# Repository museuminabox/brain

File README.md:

# brain

You're probably looking for https://github.com/museuminabox/brain/blob/master/INSTALL.md.

When you get your Museum in a Box, the box knows which objects are in it and can tell you things about them. That's because of The Brain, a microcomputer like a Raspberry Pi. There are a few peripherals too, like an RFID reader, speakers, and a screen. The brain also keeps a note of any time an object comes across it. This is called the BOOP LOG.

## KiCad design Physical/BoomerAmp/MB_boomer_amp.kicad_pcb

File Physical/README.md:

# Physical Details of the Brain

This folder holds things relating to the physical instantiation of the Brain (rather than the software installed on it).

That includes things like the design files for laser-cut enclosures, and design files for [any custom PCB](BootProgressBoard/).

## Wiring

These wiring details use [this Raspberry Pi GPIO connector diagram](http://elinux.org/RPi_Low-level_peripherals#Model_A.2B.2C_B.2B_and_B2) for labels.

### RFID Reader

|Connector P1 (l-r)|Raspberry Pi|
|------------------|------------|
|VCC|+3V3|
|IN|Not connected|
|SDA|GPIO2/SDA1|
|SCL|GPIO3/SCL1|
|OUT|GPIO4|
|GND|GND|

### BootProgressBoard

|Connector P1 (l-r)|Raspberry Pi|
|------------------|------------|
|1|GPIO24|
|2|GPIO25|
|3|GPIO17|
|4|GPIO27|
|5|GPIO22|
|6|GPIO23|
|7|GPIO10|
|8|+3V3|
|9|GND|

### Raspberry Pi 2/3

Audio is provided by an amplifier board connected to the 3.5mm jack on the Pi.

See [here for a diagram showing the 3.5mm connections](http://www.raspberrypi-spy.co.uk/2014/07/raspberry-pi-model-b-3-5mm-audiovideo-jack/)

|Amp|3.5mm jack on the Pi|
|---|--------------------|
|Left|Tip|
|Right|Ring 1|
|Ground|Ring 2|
|Not connected|Sleeve|

### Raspberry Pi Zero

Audio is provided by a DAC board.  Either the [Pimoroni pHat DAC](https://shop.pimoroni.com/products/phat-dac) with stackable headers; or the [Adafruit I2S DAC/Amp board](https://learn.adafruit.com/adafruit-max98357-i2s-class-d-mono-amp/overview).

For the DAC/Amp the connections are as follows:

|DAC/Amp board|Raspberry Pi|
|-------------|------------|
|LRC|GPIO19/MISO|
|BCLK|GPIO18|
|DIN|SCLK/GPIO21|
|GAIN|Not connected|
|SD|Not connected|
|GND|GND|
|Vin|+5V|

Because the DACs don't have volume controls, we add two buttons for volume up and down.  They're connected as follows (l-r in [this photo](https://www.flickr.com/photos/amcewen/31221595945/)):

|Volume board|Raspberry Pi|
|------------|------------|
|Volume up|GPIO6|
|Volume down|GPIO13|
|Ground|GND|
|Pin with neither button but both resistors|Not connected|

## Assembly

This isn't necessarily the *only* way to assemble the Brain, but the general order that we've taken.

### Assemble "base of the skull"

1. Assemble an [audio circuit](#Wiring_the_audio_circuit)
1. Assemble an amp-to-speaker wiring loom
1. Carefully bend the terminals on the speaker so that they form a right-angle
1. Test assemble the speaker frame and then glue it together with the speaker inside
1. Plug in the 3.5mm audio jack to connect the audio circuit to the Raspberry Pi
1. Fit the rivets into the base first
1. Push Raspberry Pi down onto the rivets in the base

### Assemble "top of the skull"

1. Lay out all the components to check that you've got everything.
1. Insert the 4 t-nuts into the base of the top
1. Solder the right-angle header onto the RFID reader
1. Test assemble the RFID reader frame, and then glue together
1. Check the fit for the pieces making up the main box
1. Glue together the pieces for the main box, apart from the top
1. Once the main box is dry, glue in the top
1. Sand down the box (if it's not acrylic)
1. Apply one or two coats of Danish oil to the box (similarly if it's not acrylic)

### Wiring the Boot Progress PCB

1. Solder up the Boot Progress Board PCB

### Wiring the audio circuit

1. For the analogue amplifier Brains, solder header pins into the amplifier
1. We use pre-assembled [cables connected to a TRRS 4-pole 3.5mm jack plug](http://uk.farnell.com/cliff-electronic-components/fc68122c/cable-assembly-jack-plug-4-way/dp/2470995?CMP=i-bf9f-00001000) to connect to the Pi, so check that which wire colour goes to which pole on the plug.  If you're soldering your own wires to a 3.5mm plug, then obviously you'll know which is which.  In our case the colour-coding is:
  * Tip: red
  * Ring 1: white
  * Ring 2: black
  * Sleeve: shielding
  Or for the double-ended cables we're using in v1, the colour-coding is:
  * Tip: red
  * Ring 1: white
  * Ring 2: green
  * Sleeve: blue or black
1. Assuming you're using the same [3.5mm switched audio jack](http://www.digikey.co.uk/product-detail/en/cui-inc/SJ1-3535/CP1-3535-ND/738693) as we do, then connect the following connections to wire the 4-pole TRRS plug to the aux audio jack:
  * Tip (red) to connection 2
  * Ring 1 (white) to connection 3
  * Ring 2 (black/green) to connection 1
  * Sleeve is left unconnected
1. If you're using the same amplifier board as us, you should desolder the audio jack from it.  When you have, the connections&mdash;when viewed from underneath, from left to right&mdash;are tip \ sleeve / ring (on a TRS stereo jack)
1. Wire the output connections of the aux jack to the amplifier, with ~20cm of cable.  We'll leave the ground connection unconnected as it will prevent a ground loop with the ground connection for power.
  * Connection 4 (red) to the left audio input
  * Connection 5 (white) to the right audio input

### Prep the amp-to-speaker wiring loom

1. Cut a 15cm length of 2-core cable
1. Bare ~5mm of wire at one end and tin the end
1. Bare ~10mm of wire at the other end
1. Insert the longer bared ends through the loops on the terminals on the speaker (if you've got coloured wire, red to positive and black to negative) then fold it back on itself to make a decent physical connection.  Then solder the wires to the speaker terminal

### Assemble main wiring loom

1. Get the RFID to Pi connector cable
1. Wire a two-pin shroud to the 5V and ground connection on the RFID reader shroud to break out power from the Raspberry Pi to the amplifier
1. Assemble the Boot Progress PCB wiring loom with 9-pin shroud and [connections as detailed above](#BootProgressBoard)

### Assembly
1. Fasten the USB extension cable into the main box
1. Connect up all the electronics and make sure it's all working before it gets installed fully
1. Fit the amp and 3.5mm jack socket into the main box
1. Hot-glue the boot progress board into the main box

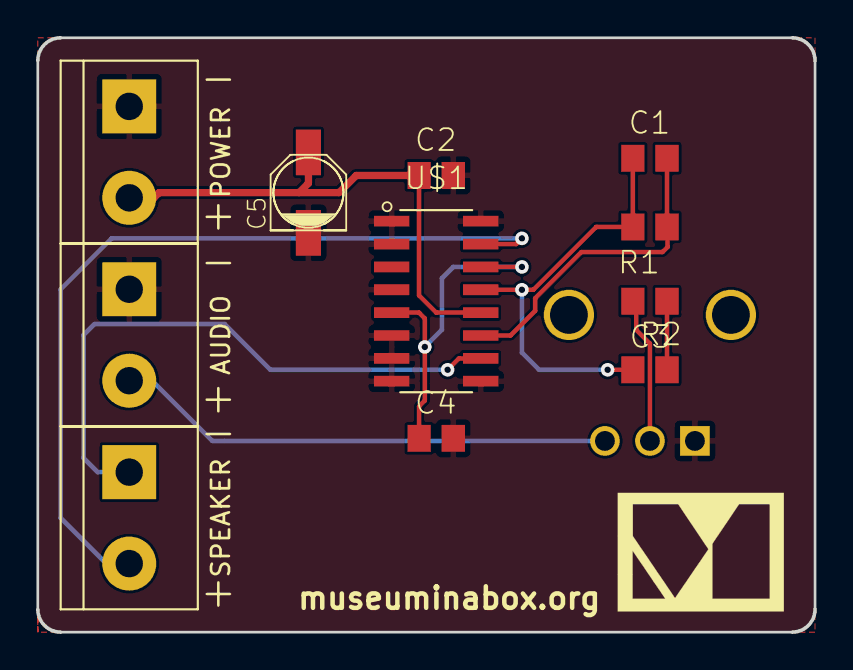
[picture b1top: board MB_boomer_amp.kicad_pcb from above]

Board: 2 copper layers, 43.2 x 33.0 mm, 12 parts (0 on the bottom side), 10 nets.

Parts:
AUDIO: GREEN-2P-3.5; TerminalBlock_bornier-2_P5.08mm
C1: 5p; C0805
C2, C4: 100n; C0805
C3: 4.7u; C0805
C5: 10u; PANASONIC_B
POWER: GREEN-2P-3.5; TerminalBlock_bornier-2_P5.08mm
R1: 100k; R0805
R2: 10k; R0805
SPEAKER: GREEN-2P-3.5; TerminalBlock_bornier-2_P5.08mm
U$1: LM4860; SOIC127P600X175-16
VR1: 9MM_SNAP-IN_POT_; 9MM_SNAP-IN_POT

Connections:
/ASIG: AUDIO.2, VR1.3
/VCC: C2.1, C5.+, POWER.2, U$1.12
GND: AUDIO.1, C2.2, C4.2, C5.-, POWER.1, U$1.1, U$1.2, U$1.4, U$1.6, U$1.7, U$1.8, U$1.9, U$1.16, VR1.1
unnamed: C1.1, R1.2, R2.1, U$1.13
unnamed: C1.2, R1.1, U$1.11
unnamed: C3.1, R2.2
unnamed: C3.2, VR1.2
unnamed: C4.1, U$1.5, U$1.14
unnamed: SPEAKER.1, U$1.10
unnamed: SPEAKER.2, U$1.15

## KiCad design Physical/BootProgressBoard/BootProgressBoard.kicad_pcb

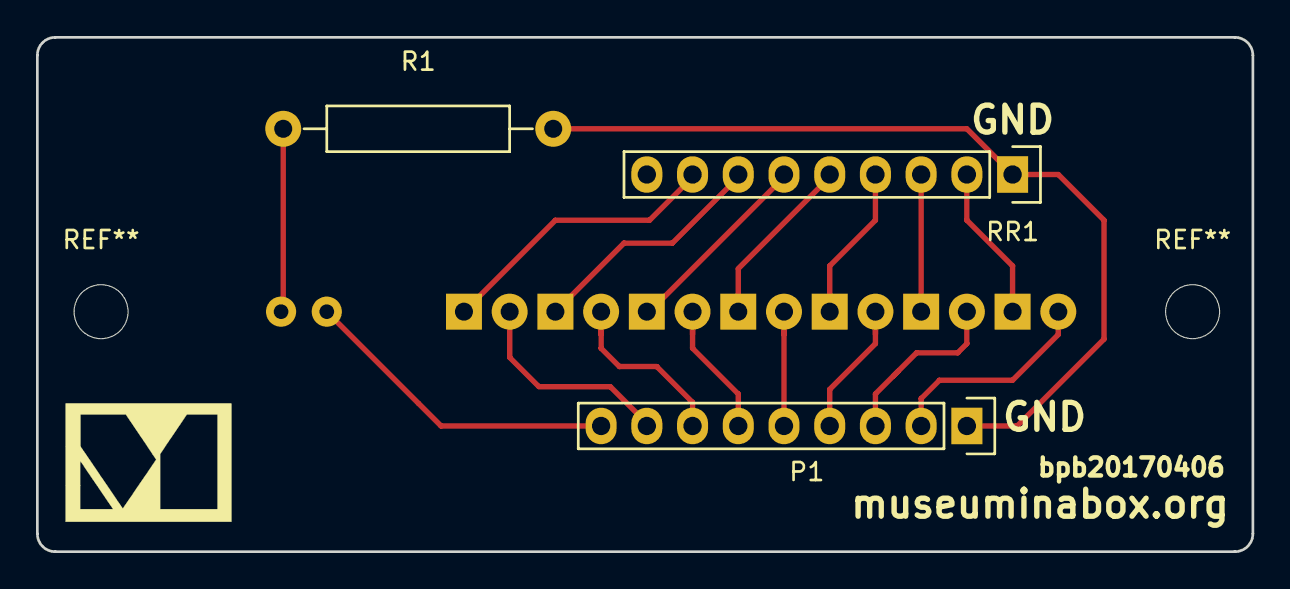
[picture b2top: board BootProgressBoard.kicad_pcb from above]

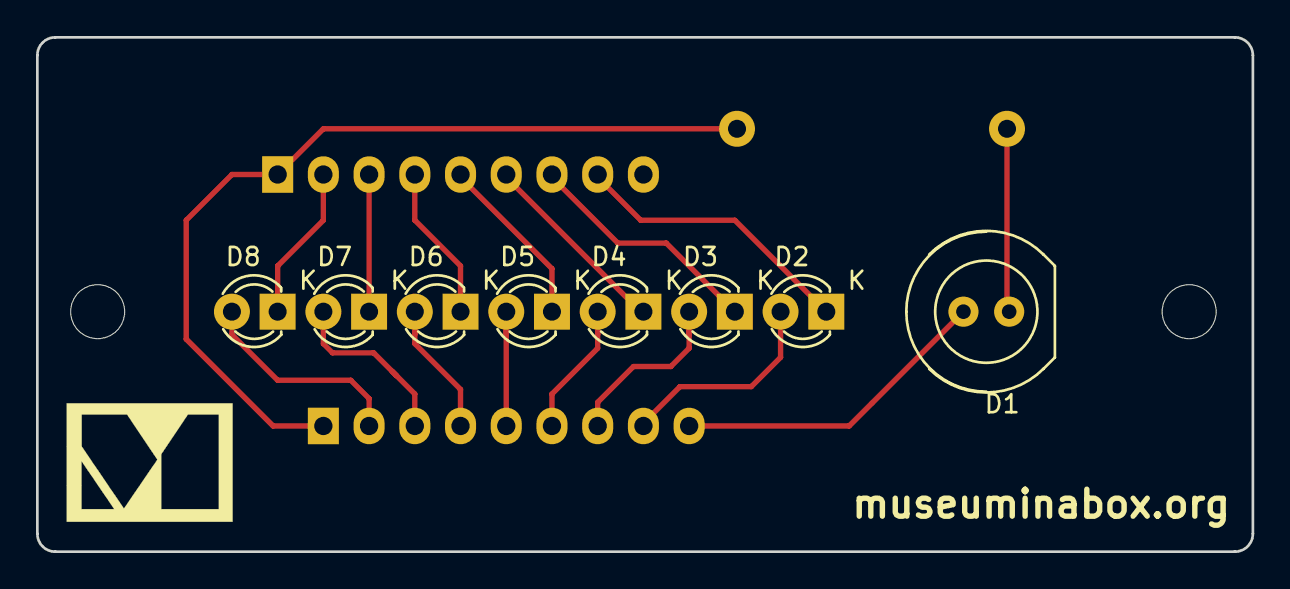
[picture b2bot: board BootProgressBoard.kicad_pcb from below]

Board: 2 copper layers, 67.5 x 28.6 mm, 11 parts (8 on the bottom side), 17 nets.

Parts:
D1: LED; LED-8MM
D2, D3, D4, D5, D6, D7, D8: LED; LED-3MM
P1: CONN_01X09; Socket_Strip_Straight_1x09
R1: R; Resistor_Horizontal_RM15mm
RR1: RR8; Socket_Strip_Straight_1x09

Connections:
unnamed: D1.1, R1.1
unnamed: D1.2, P1.9
unnamed: D2.1, RR1.8
unnamed: D2.2, P1.8
unnamed: D3.1, RR1.7
unnamed: D3.2, P1.7
unnamed: D4.1, RR1.6
unnamed: D4.2, P1.6
unnamed: D5.1, RR1.5
unnamed: D5.2, P1.5
unnamed: D6.1, RR1.4
unnamed: D6.2, P1.4
unnamed: D7.1, RR1.3
unnamed: D7.2, P1.3
unnamed: D8.1, RR1.2
unnamed: D8.2, P1.2
unnamed: P1.1, R1.2, RR1.1

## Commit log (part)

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2015-12-01 Initial version.
2015-12-01 Add Node RED flow for the video brain.
2015-12-01 Add Node RED flow for the audio brain.
2015-12-01 Extend form entry fields.
2015-12-01 Add instructions for writing tags
2015-12-07 Add laser-cutting file for self-contained MiaB.
2015-12-07 Log Boops to local CSV and web (for video boxes)
2015-12-07 Update audio version to submit Boops to the cloud.
2015-12-10 Add script to ease writing RFID tags.
    Needs libfreefare, and a PN532 USB NFC reader (or presumably something else that libfreefare/libnfc can drive)
2016-04-02 Make brain setup easier. Most of issue #17.
    Merge audio and video flows together - chooses behaviour at run time based on context.global.box_settings.brain_type
    Load settings (from /home/pi/miab/box-config.json) on startup and store them in context.global.box_settings
    Add a web UI '/setup' which downloads a list of boxes from www.museuminabox.org and gives you a simple drop-down menu to choose which box this brain is inside
    Add a web UI '/prints' (which you get redirected to from a successful submission on '/setup') which lists prints for this box and provides a 'Write tag' button next to each
    Add code to write print's NFC tag content to a tag when the 'Write tag' button is clicked
2016-04-11 Added more detailed instructions for WiFi 📡
2016-04-11 Add downloading of Brain content from website, playing ready.wav when the brain is ready to work
2016-05-12 Update for battery & volume control version of the brain.
2016-05-13 Add the display card template and other handy-but-non-essential files.
2016-05-20 Faster tag recognition by using the GPIO "tag present" signal.
2016-05-25 Added some labels and explanation to the case design
2016-05-25 Move object-detected-boop to only happen with video Brains
2016-05-25 Add files to indicate boot progress
2016-06-08 Add frog case design.
2016-06-15 Start ansible configuration for bootstrapping a Brain.
2016-07-12 Finish provisioning brains via ansible.
    Two roles created:
    * A base Node RED install
    * A Node RED install with an RFID reader
    Then sets up the MiaB brain on top of that.
    Boot progress script moved to systemd (in line with newer Raspbian)
    NDEF reading C program from simple_sl030_rfid_reader compiled and included in the miab/ folder, along with a service to copy the correct one to a common filename on boot (so will work regardless of t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
2016-08-16 Update RFID reading binary to work better on a Pi3
2016-08-23 Fix a couple of bugs in the ansible script.
    Bits missed during development as I'd obviously installed things and/or run Node RED before working out which files were needed. Running through the process from a bare SD card showed up a few bits t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
2016-09-06 Switch back to wpa_supplicant.conf (from wicd-curses) for WiFi management
2016-09-08 Finished provisioning work.
    * /setup now correctly downloads all the content when run, rather than needing to wait for next boot (was passing through parts of old web requests to the "download list of box contents" request, whi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
    * Hostname is set to brain
2016-09-22 Add soundcard configuration to use a Phat DAC on the Pi Zero
2016-09-22 Switch to sox for audio playback (copes with different sample rates)
2016-09-22 Set volume to max during provisioning. Fixes #28
2016-09-22 Pre-set the content folders so they don't end up owned by root. Fixes #27
2016-09-28 Stop git caring about brain images
2016-09-28 Add micro:bit code for Brain to talk to microbit-miab
2016-09-28 Update case to micro-USB power, using Boot Progress Board PCB
2016-09-28 Add spacer to make the LEDs line up better above the PCB
2016-10-04 Set up USB sound card as the one to use for recording
2016-10-17 Just replacing after a George github tutorial
2016-10-19 MVP of recording user content.
    The replay/delete/save buttons are accessed at http://brain.local:1880/ rather than as physical buttons at present.
2016-11-07 Change user the boot progress script runs as, so the LEDs light up again.
2016-12-06 Add wiring instructions
2017-03-03 Change booting sound files to Gill
2017-03-03 First pass at Pi3 timings for boot progress
2017-03-17 Add instructions for using the pre-rolled image files
2017-03-17 Tweak the volume level for the brains
2017-03-17 Update progress/ready audio cues (to Gill)
2017-03-27 Tweaks for RPi3 timings for the LEDs. Fixes #25
2017-03-27 Set umask so downloaded content can be modified by the pi user. Fixes #32
2017-04-11 Drop www. from URL, move logo & URL
2017-07-17 Gill's intro script
2017-09-13 Latest version
2017-09-13 Add assembly instructions
2017-09-13 Work-in-progress WiFi config. Start of Resin-wifi-connect addition.
    Manual steps required afterwards:
    * Run through the steps in the Dockerfile
    * Mod /usr/src/app/src/hotspot.js to stop the dnsmasq service before the hotspot is created
2017-09-13 Add w-i-p service file to start the WiFi config at boot
2017-09-13 Move Gill intro audio to where the Brains can play it.
2017-09-25 Make pre-rolled image install docs section clearer
2018-01-12 rough startup scripts
2018-02-14 Set WiFi settings for known networks
2018-02-14 Use a special RFID tag to launch wifi configuring.
    Also fixed bug so it plays the right message when the WiFi config script starts.
    And add ability to write the config tags to http://brain.local:1880/prints
2018-02-15 Remove unused wifi configure service script
2018-02-24 Remove support for video playback. Fixes #44
2018-02-24 Revert to original version of raspi_version.py. Fixes #42
2018-02-26 Change boop example to reflect reality
2018-02-28 Add updates about UUIDs.
2018-03-02 Move to new box creation workflow. Part of #52.
    Not fully tested yet because the corresponding Heart API hasn't been built.
2018-03-07 Record boop ends as well as boop starts. UNTESTED. Part of #40
    Need the corresponding part in the Heart app to be implemented before we can test this.
2018-03-07 Change computer name from 'brain' to 'box'. Fixes #53
2018-03-13 Rework wiring loom for simpler assembly. Fixes #57
2018-03-14 Move to new heart.museuminabox.org/api endpoints and avoid startup race condition.
    * Fixes #26 - point at heart.museuminabox.org
    * Fixes #60 - move API calls to /api/...
    * Fixes #61 - race condition at startup
2018-03-14 Fix bug where the headers weren't set for the box creation call. Now tested and working, last part of #52
2018-03-14 Update details for Boop start and end endpoints
2018-03-14 Formatting fix
2018-03-15 Add hardware_id details.
2018-03-15 Add hardware_id and exterior etc.
2018-03-15 Fix List of Prints response
2018-03-15 Submit hardware_id and exterior when creating a box, and send boop_id when boops end.
    Fixes #63 - store hardware_id and exterior
    Fixes #42 - boop ends and boop starts recorded
2018-03-15 Add software versioning. UNTESTED Needs corresponding Heart changes.
    Most of #56
2018-03-15 Fix Box Sync endpoint (only UUIDs)
2018-03-21 Updates to build instructions following the latest round of manufacturing
2018-04-11 Add `/upgrade` option. Fixes #64. Also shows existing ID if set. Fixes #71
2018-04-13 WiFi config now gives up after 2 mins, and tells you if it worked or not. Fixes #67
2018-04-13 Change WiFi branding to MiaB. Fixes #72
2018-04-13 copy tweaks
2018-04-14 Improve display of `/prints` screen. Part of #73
2018-04-14 Speed up boot progress bar now OS is faster to boot. Part of #65
2018-04-14 Add simple upgrade process. First pass at #55.
    Also fixed print image display on `/prints`, part of #73
2018-04-14 Change default password. First fix for #54
2018-04-14 Update version number for the latest features.
2018-05-21 Add work-around Wifi config for 802.1x networks. Part of #78
2018-05-21 Bump version number for work-around wifi config changes.
2018-05-29 Add instructions for configuring wifi and checking for updates.
2018-05-29 Fix links to embedded images
2018-10-09 we need to document a whole bunch more
    about what "componentry" entails and how to get it attractively arranged :)
2018-10-22 Initial version of the amp PCB. Part of #86
2018-11-04 Add logo to the Boomer amp. Part of #86
2018-11-04 Ignore Kicad backup files
2018-11-14 New skull design for the different RFID reader. Part of #92
2018-11-14 Tweak skull filename name
2018-12-02 Jig to make it easier to glue the SL030 RFID reader in the right place
2018-12-02 Update jig for new MFRC522 RFID reader
2018-12-04 New wiring loom for the new SPI-based RFID reader
2018-12-11 Modified colour for Pimironi order
    Added green for a kiss cut
2018-12-11 v1.2 files for ply and acrylic for
    New skull files in acrylic and ply from Paul at Pimironi, used to cut
    the batch of 80 boxes in November.
2018-12-11 Acrylic reader spacers
    3mm clear acrylic replacement reader spacers for flipped readers in 18x
    transparent boxes
2018-12-11 Skull reader spacers update
    Update to line colours and weighting for quotes from local cutters
2018-12-13 Update wifi-connect repo to cope with Resin.io's rename. Fixes #95
2018-12-17 Remove the "soft" volume support, as we're not using it. Fixes #102
2018-12-17 Improve downloading of audio content (and tweaks to /upgrade). Fixes #76 and most of #100
2018-12-18 Update build script and flow for new RC522 RFID reader. Part of #92
2018-12-18 Add Gillian object to all collections (hard-coded in /prints). Fixes #68
2018-12-18 Group prints on `/prints` by collection. Most of #101
2018-12-18 Play any object audio after the "ok ready to go" rather than at same time. Fixes #50
2018-12-19 Update to George-voiced welcome audio. Part of #68
2018-12-19 Moved NodeRED debug to /admin, changed port to 80. Most of #83
2018-12-19 Fix a couple of bugs having moved /admin. Part of #68
2018-12-19 Change port back to 1880 to prevent problems with the WiFi config. Part of #83
2018-12-19 Add a 1s delay between the "ok, ready to go" and object audio. Part of #50
2018-12-19 Report MAC address to heart, to aid with WiFi setup in weird cases. Brain part of #82
2018-12-21 Limit box exterior options to controlled set. Fixes #103
2018-12-21 Cope with any problems with reading the WiFi MAC address (and send "" instead). Part of #82
2018-12-21 Update WiFi, updates, etc. audio. Part of #75
2018-12-21 Update WiFi config UI for latest version of the connect info. Part of #95 and #78.
2018-12-23 Update instructions for the new wiring loom. Part of #104
2019-01-15 Bump version number (as we've shipped the last version)
2019-01-16 Tweak timing and dependency list so the soundcard is ready when we play the "one moment please" audio. Fixes #87
2019-01-16 Use correct *print* ID for the Gillian totems. Fixes #68
2019-01-19 Update wording on advanced wifi page, for #106
2019-01-20 Add images for the WiFi and Update cards. Fixes #107
2019-01-24 Add God From the Sea initial object. Fixes #108
2019-05-15 Submit box's IP address when checking for new content. Part of #185
2019-09-02 Add support for Model A (make it use the DAC for sound)
2019-09-25 Major upgrade to take boxes with earlier SL030 RFID reader hardware to parity with 0.9.6 of master. Fixes #118.
2019-09-25 Add file missed in the previous commit. Part of #118
2019-09-26 Update to Resin/Balena WiFi config tool.
2019-09-30 Corrected progress LEDs for Pioneer hardware. Part of #118
2019-09-30 Fix bug showing multiple collections on `/prints`. Part of #118
2019-10-21 Seemed to need a marker to make Ansible *actually* apply the RTC changes. Final part of https://github.com/museuminabox/brain-dei-mille/issues/1
2019-11-06 Check for config at boot, play alert message if not found
2019-11-06 Use proper check in shell script
2019-11-08 Updates for new `box-config.json` location. Most of #126
    * Moved check for config file (and playing of warning audio) to NodeRED
    * Removed `/setup` and `/upgrade` pages from box.local web UI (as they'll be handled elsewhere)
2019-11-18 Only report "config file not found" if the file read fails, not general errors. Part of #126
